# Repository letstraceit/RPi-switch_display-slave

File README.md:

# RPi-switch_display-slave
Raspberry Pi slave board with 3 port Ethernet switch and output for RGB LED matrix.

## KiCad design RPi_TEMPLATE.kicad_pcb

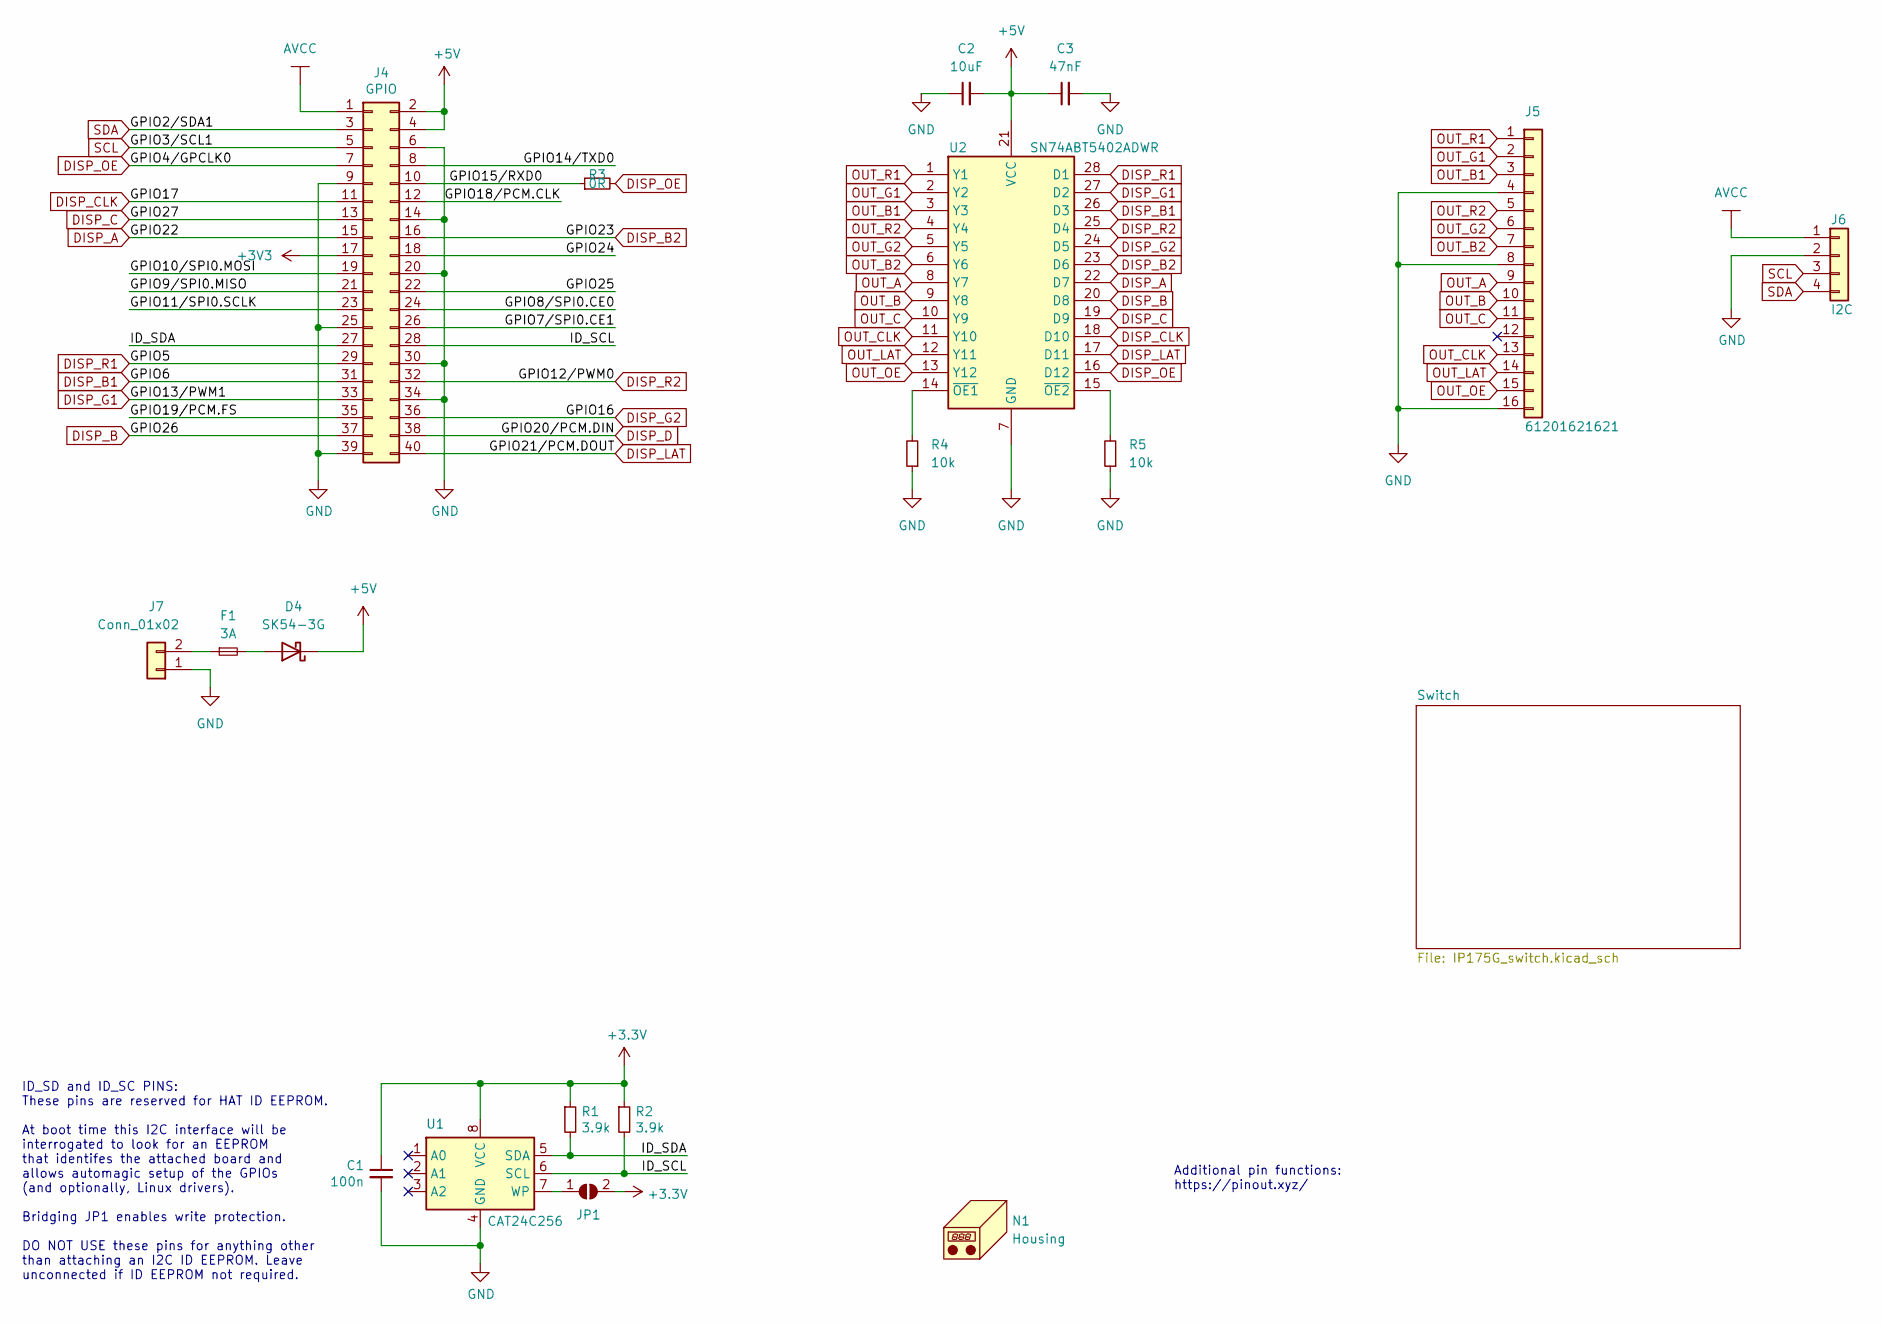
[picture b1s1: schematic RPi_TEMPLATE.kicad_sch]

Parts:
C1: 100n; C_0402_1005Metric
C2: 10uF; C_0603_1608Metric
C3: 47nF; C_0603_1608Metric
D4: SK54-3G; DO-214AA-2
F1: 3A; Fuse_1206_3216Metric
J4: GPIO; PinSocket_2x20_P2.54mm_Vertical
J5: 61201621621; 61201621621_2x8-2.54
J6: I2C; PinHeader_1x04_P2.54mm_Vertical
J7: Conn_01x02; 01X02_5mm_pitch
JP1: ID_WP; SolderJumper-2_P1.3mm_Open_RoundedPad1.0x1.5mm
N1: Housing; treceit
R1, R2: 3.9k; R_0603_1608Metric
R3: 0R; R_0603_1608Metric
R4, R5: 10k; R_0603_1608Metric
U1: CAT24C256; SOIC127P600X175-8N
U2: SN74ABT5402ADWR; SOIC127P1030X265-28N; Mouser Part Number 595-SN74ABT5402ADWR

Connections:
+5V: C2.2, C3.1, D4.1 (K), J4.2, J4.4, U2.21 (VCC)
/GPIO7/SPI0.CE1: J4.26
/GPIO8/SPI0.CE0: J4.24
/GPIO9/SPI0.MISO: J4.21
/GPIO10/SPI0.MOSI: J4.19
/GPIO11/SPI0.SCLK: J4.23
/GPIO14/TXD0: J4.8
/GPIO15/RXD0: J4.10, R3.1
/GPIO18/PCM.CLK: J4.12
/GPIO19/PCM.FS: J4.35
/GPIO24: J4.18
/GPIO25: J4.22
/ID_SCL: J4.28, R2.2, U1.6 (SCL)
/ID_SDA: J4.27, R1.2, U1.5 (SDA)
AVCC: J4.1, J6.1; also elsewhere on the board
DISP_A: J4.15, U2.22 (D7)
DISP_B: J4.37, U2.20 (D8)
DISP_B1: J4.31, U2.26 (D3)
DISP_B2: J4.16, U2.23 (D6)
DISP_C: J4.13, U2.19 (D9)
DISP_CLK: J4.11, U2.18 (D10)
DISP_D: J4.38
DISP_G1: J4.33, U2.27 (D2)
DISP_G2: J4.36, U2.24 (D5)
DISP_LAT: J4.40, U2.17 (D11)
DISP_OE: J4.7, R3.2, U2.16 (D12)
DISP_R1: J4.29, U2.28 (D1)
DISP_R2: J4.32, U2.25 (D4)
GND: C1.2, C2.1, C3.2, J4.6, J4.9, J4.14, J4.20, J4.25, J4.30, J4.34, J4.39, J5.4, J5.8, J5.16, J6.2, J7.1, R4.1, R5.1, U1.4 (GND), U2.7 (GND); also elsewhere on the board
unnamed: D4.2 (A), F1.2
unnamed: F1.1, J7.2
unnamed: JP1.1 (A), U1.7 (WP)
unnamed: R4.2, U2.14 (~OE1)
unnamed: R5.2, U2.15 (~OE2)
OUT_A: J5.9, U2.8 (Y7)
OUT_B: J5.10, U2.9 (Y8)
OUT_B1: J5.3, U2.3 (Y3)
OUT_B2: J5.7, U2.6 (Y6)
OUT_C: J5.11, U2.10 (Y9)
OUT_CLK: J5.13, U2.11 (Y10)
OUT_G1: J5.2, U2.2 (Y2)
OUT_G2: J5.6, U2.5 (Y5)
OUT_LAT: J5.14, U2.12 (Y11)
OUT_OE: J5.15, U2.13 (Y12)
OUT_R1: J5.1, U2.1 (Y1)
OUT_R2: J5.5, U2.4 (Y4)
SCL: J4.5, J6.3
SDA: J4.3, J6.4

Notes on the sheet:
Additional pin functions: https://pinout.xyz/
ID_SD and ID_SC PINS: These pins are reserved for HAT ID EEPROM. At boot time this I2C interface will be interrogated to look for an EEPROM that identifes the attached board and allows automagic setup of the GPIOs (and optionally, Linux drivers). Bridging JP1 enables write protection. DO NOT USE th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

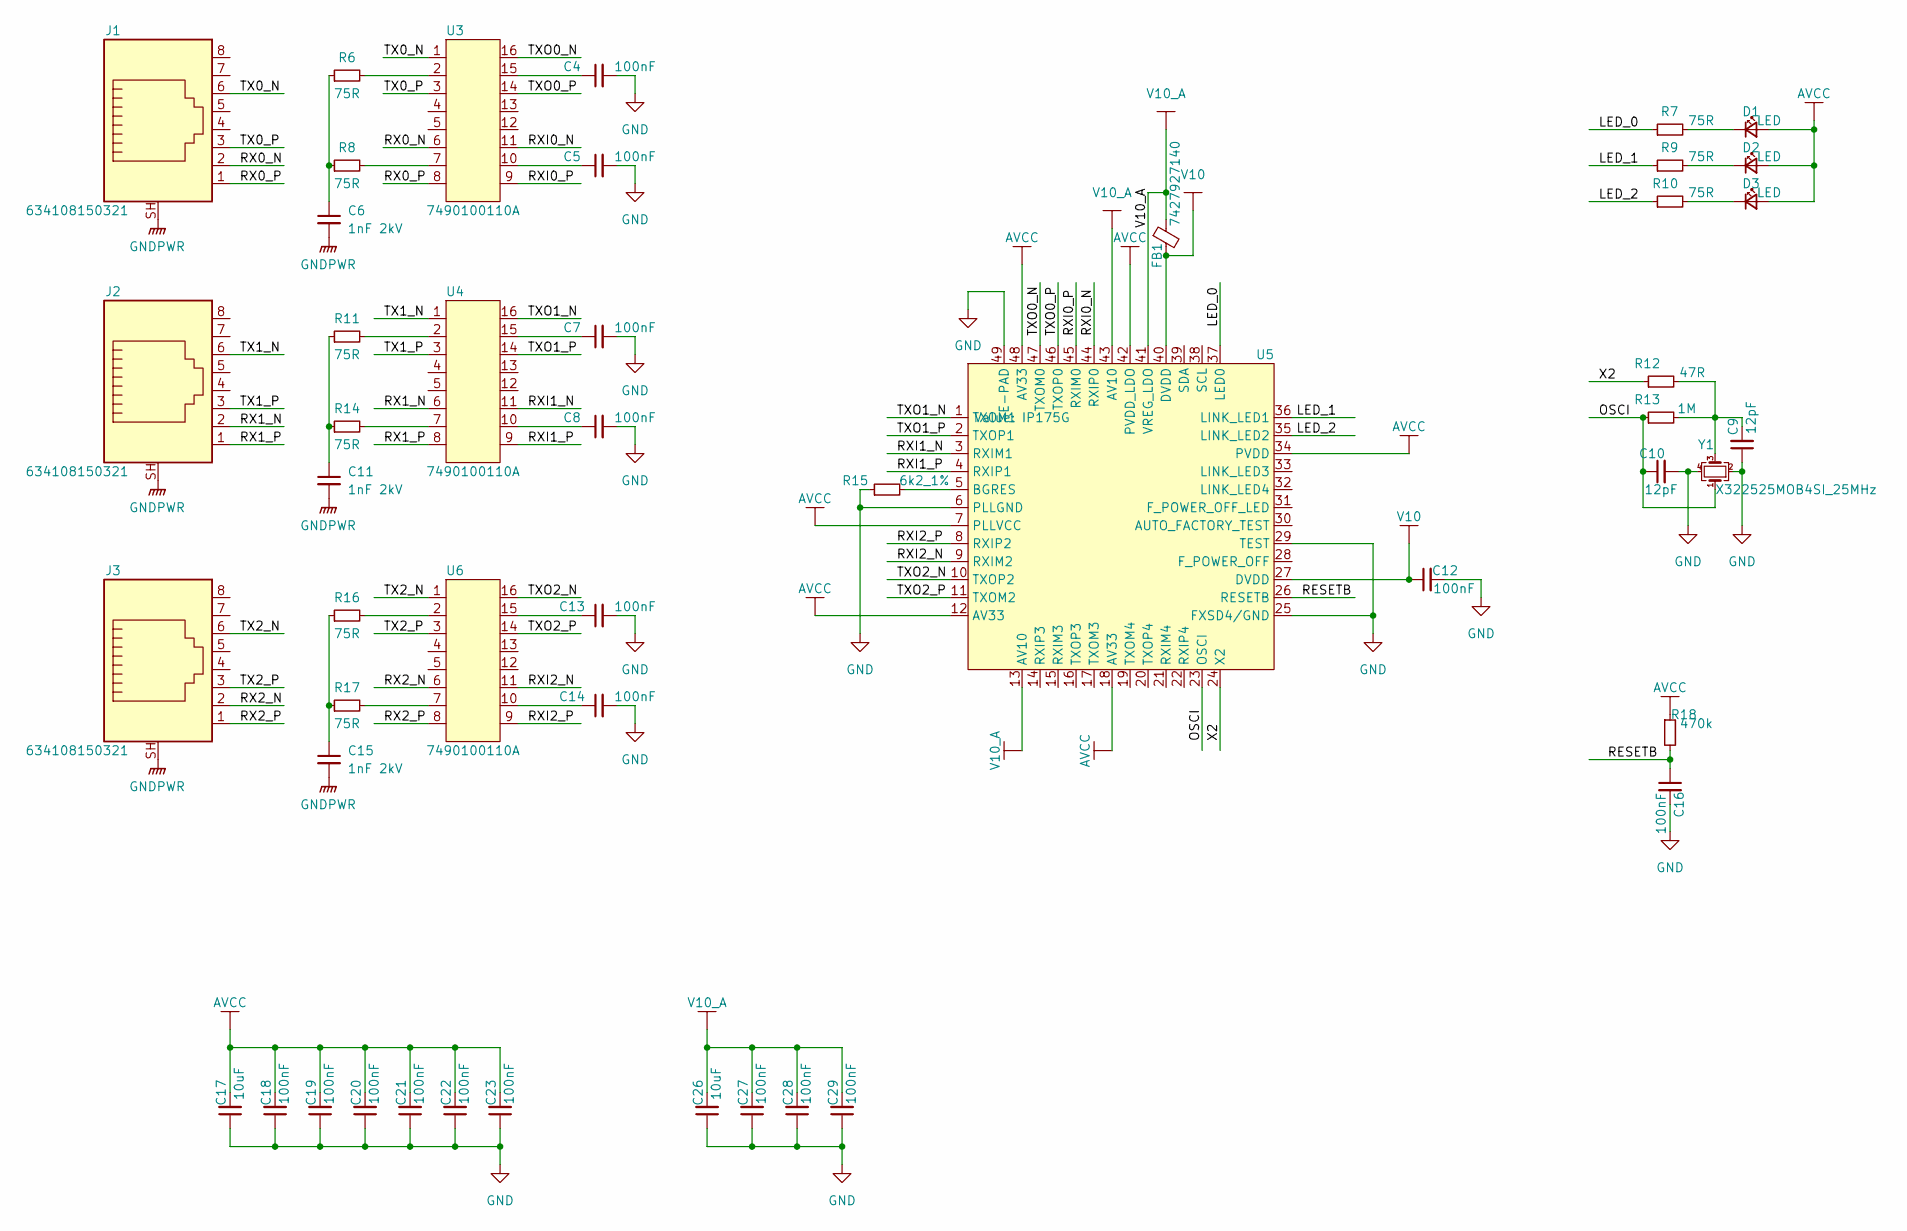
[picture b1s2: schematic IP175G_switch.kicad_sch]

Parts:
C4, C5, C7, C8, C12, C13, C14, C16, C18, C19, C20, C21, C22, C23, C27, C28, C29: 100nF; C_0402_1005Metric
C6, C11, C15: 1nF 2kV; C_1206_3216Metric
C9, C10: 12pF; C_0402_1005Metric
C17, C26: 10uF; C_0603_1608Metric
D1, D2, D3: LED; LED_0603_1608Metric
FB1: 7427927140; C_0402_1005Metric
J1, J2, J3: 634108150321; 634108150321_RJ45
R6, R7, R8, R9, R10, R11, R14, R16, R17: 75R; R_0603_1608Metric
R12: 47R; R_0603_1608Metric
R13: 1M; R_0603_1608Metric
R15: 6k2_1%; R_0603_1608Metric
R18: 470k; R_0603_1608Metric
U3, U4, U6: 7490100110A
U5: IP175G; QFN40P600X600X90-49N-D
Y1: X322525MOB4SI_25MHz; ECS327TXO33TR

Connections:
/Switch/LED_0: R7.1, U5.37 (LED0)
/Switch/LED_1: R9.1, U5.36 (LINK_LED1)
/Switch/LED_2: R10.1, U5.35 (LINK_LED2)
/Switch/OSCI: C10.1, R13.1, U5.23 (OSCI), Y1.1
/Switch/RESETB: C16.1, R18.2, U5.26 (RESETB)
/Switch/RX0_N: J1.2, U3.6
/Switch/RX0_P: J1.1, U3.8
/Switch/RX1_N: J2.2, U4.6
/Switch/RX1_P: J2.1, U4.8
/Switch/RX2_N: J3.2, U6.6
/Switch/RX2_P: J3.1, U6.8
/Switch/RXI0_N: U3.11, U5.44 (RXIP0)
/Switch/RXI0_P: U3.9, U5.45 (RXIM0)
/Switch/RXI1_N: U4.11, U5.3 (RXIM1)
/Switch/RXI1_P: U4.9, U5.4 (RXIP1)
/Switch/RXI2_N: U5.9 (RXIM2), U6.11
/Switch/RXI2_P: U5.8 (RXIP2), U6.9
/Switch/TX0_N: J1.6, U3.1
/Switch/TX0_P: J1.3, U3.3
/Switch/TX1_N: J2.6, U4.1
/Switch/TX1_P: J2.3, U4.3
/Switch/TX2_N: J3.6, U6.1
/Switch/TX2_P: J3.3, U6.3
/Switch/TXO0_N: U3.16, U5.47 (TXOM0)
/Switch/TXO0_P: U3.14, U5.46 (TXOP0)
/Switch/TXO1_N: U4.16, U5.1 (TXOM1)
/Switch/TXO1_P: U4.14, U5.2 (TXOP1)
/Switch/TXO2_N: U5.10 (TXOP2), U6.16
/Switch/TXO2_P: U5.11 (TXOM2), U6.14
/Switch/X2: R12.1, U5.24 (X2)
AVCC: C17.2, C18.2, C19.2, C20.2, C21.2, C22.2, C23.2, D1.2 (A), D2.2 (A), D3.2 (A), R18.1, U5.7 (PLLVCC), U5.12 (AV33), U5.18 (AV33), U5.34 (PVDD), U5.42 (PVDD_LDO), U5.48 (AV33); also elsewhere on the board
GND: C4.2, C5.2, C7.2, C8.2, C9.1, C10.2, C12.2, C13.2, C14.2, C16.2, C17.1, C18.1, C19.1, C20.1, C21.1, C22.1, C23.1, C26.1, C27.1, C28.1, C29.1, R15.1, U5.6 (PLLGND), U5.25 (FXSD4/GND), U5.29 (TEST), U5.49 (E-PAD), Y1.2, Y1.4; also elsewhere on the board
GNDPWR: C6.2, C11.2, C15.2, J1.SH, J2.SH, J3.SH
unnamed: C4.1, U3.15
unnamed: C5.1, U3.10
unnamed: C6.1, R6.1, R8.1
unnamed: C7.1, U4.15
unnamed: C8.1, U4.10
unnamed: C9.2, R12.2, R13.2, Y1.3
unnamed: C11.1, R11.1, R14.1
unnamed: C13.1, U6.15
unnamed: C14.1, U6.10
unnamed: C15.1, R16.1, R17.1
unnamed: D1.1 (K), R7.2
unnamed: D2.1 (K), R9.2
unnamed: D3.1 (K), R10.2
unnamed: R6.2, U3.2
unnamed: R8.2, U3.7
unnamed: R11.2, U4.2
unnamed: R14.2, U4.7
unnamed: R16.2, U6.2
unnamed: R17.2, U6.7
unnamed: R15.2, U5.5 (BGRES)

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
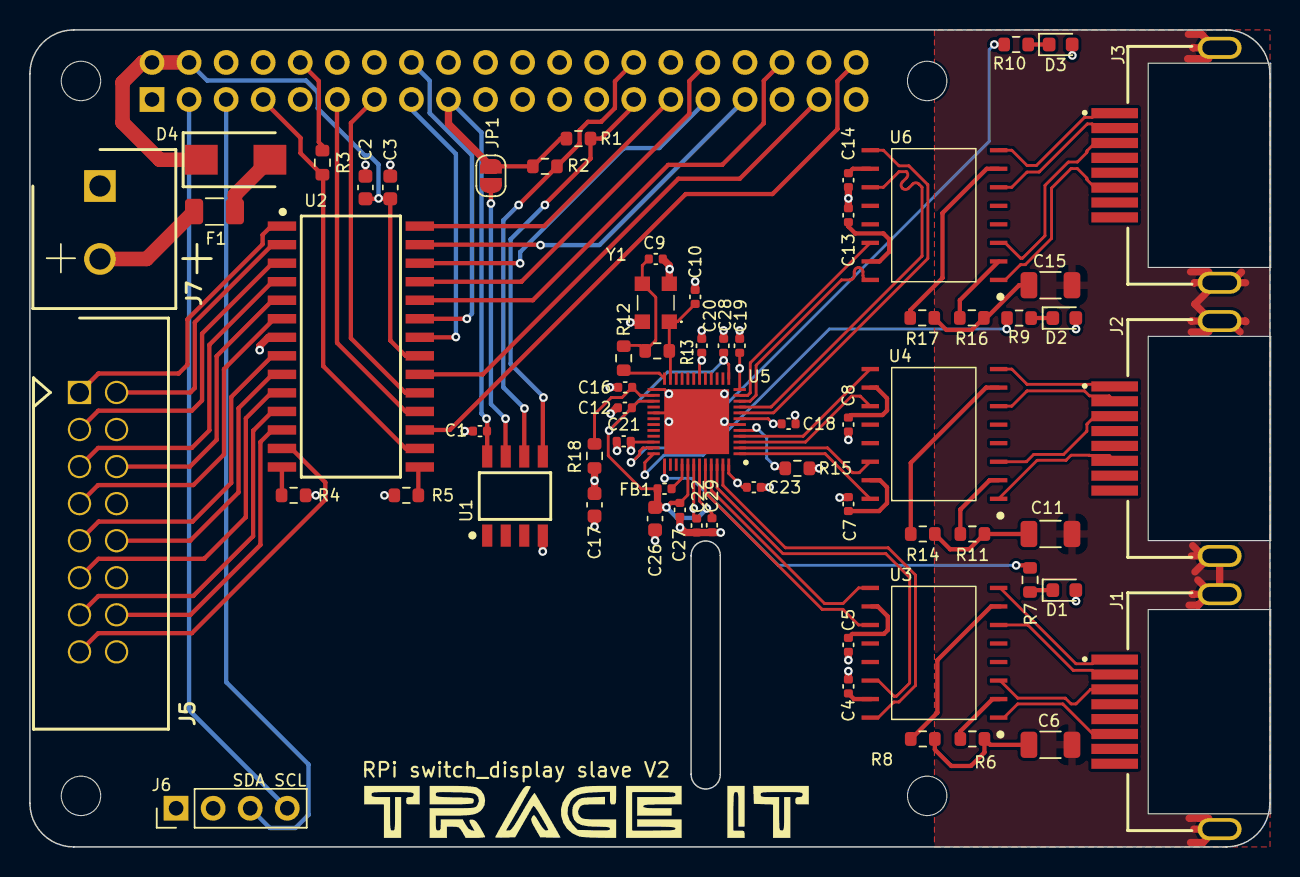
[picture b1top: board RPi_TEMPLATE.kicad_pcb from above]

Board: 4 copper layers, 85.0 x 56.0 mm, 71 parts (1 on the bottom side), 90 nets.

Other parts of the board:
MH1, MH2, MH3, MH4: MountingHole_2.7mm_M2.5

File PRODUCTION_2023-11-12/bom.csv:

Designator,Footprint,Quantity,Value,LCSC Part #
C1,402,optional,100n,Not mounted
"C10, C9",402,2,12pF,
"C11, C15, C6",1206,3,1nF 2kV,
"C12, C13, C14, C16, C18, C19, C20, C21, C22, C23, C27, C28, C29, C4, C5, C7, C8",402,17,100nF,
"C17, C2, C26",603,3,10uF,
C3,603,1,47nF,
"D1, D2, D3",603,3,LED,
D4,DO-214AA-2,1,SK54-3G ,
F1,1206,1,3A,
FB1,402,1,7427927140,
"J1, J2, J3",634108150321_RJ45,3,634108150321,
J4,PinSocket_2x20_P2.54mm_Vertical,1,ESQ-120-23-T-D,
J5,61201621621_2x8-2.54,1,61201621621,
J6,PinHeader_1x04_P2.54mm_Vertical,optional,,
J7,01X02_5mm_pitch,1,Conn_01x02,
N1,treceit,1,Housing,
"R1, R2",603,optional,3.9k,Not mounted
"R10, R11, R14, R16, R17, R6, R7, R8, R9",603,9,75R,
R12,603,1,47R,
R13,603,1,1M,
R15,603,1,6k2_1%,
R18,603,1,470k,
R3,603,1,0R,
"R4, R5",603,2,10k,
U1,SOIC127P600X175-8N,optional,CAT24C256,Not mounted
U2,SOIC127P1030X265-28N,1,SN74ABT5402ADWR,
"U3, U4, U6",7490100110A,3,7490100110A,
U5,QFN40P600X600X90-49N-D,1,IP175G,
Y1,ECS327TXO33TR,1,X322525MOB4SI_25MHz,
